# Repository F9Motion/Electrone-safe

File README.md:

# Electrone-safe
An Electronic safe with 4 numbers for password with Buzzer and Display for your snacs!

# Why I made this
My mechanical safe project was rejected so I just did electronic safe to protect my snacs.
# Features
* You can chose your password
* Display for comfort
* Protection with 4 numbers
* Custom safe
# How it works
PCB from this safe have 12 buttons(10 for numbers 3 for **ENTER** and **BACKSPACE**).
You can change your password in firmware(Soon I teach you how to do it). When you push your password firmware give command to motor and motor open safe and show text "CORRECT". And after a few moment motor close safe. When the password is incorrect safe don't open. Just give you chance to retry. And in display you see text "INCORRECT". Safe can't block but don't worry if someone try to write all combination he have to write 10 000 variants to unlock the safe. Your snacs is protected.
# How to assemble
1. Order part from BOM
2. Solder parts to PCB
3. Glue mount between case and door.
4. Flash Raspberry pi pico(read "HOW TO FLASH")
5. Place PCB to door mount.
6. Glue door mount to door
7. Put your snacs to safe!
# How to Flash
1. Download Arduino IDE
2. Open my firmware and find text **PASSWORD**
3. Change it
4. Connect pico to PC
5. Upload firmware just by clicking this button

# Bill Of Material(BOM)

|Name             |Price (without shipping)|Link (if item have a link)|
|-----------------|------------------------|--------------------------|
|Raspberry pi pico|$2.74                   |https://ali.click/bl02r1b |
|Printing PCB     |$4                      |JLCPCB                    |
|Buttons          |$2.46                   |https://ali.click/kr02r1y |
|Buzzer           |$1.64                   |https://ali.click/tt02r1c |
|Display          |$1.63                   |https://ali.click/ty02r1x |
|Battery          |$5.26                   |https://ali.click/z212r1b |
|Servo Motor      |$1.47                   |https://ali.click/q512r1s |
|buttons.step     |$0.08                   |felament price only       |
|case.step        |$8.65                   |felament price only       |
|door mount.step  |$0.05                   |felament price only       |
|door .step       |$2.22                   |felament price only       |
|mount.step       |$0.99                   |felament price only       |

# Credits
Programs: Blender, KiCad, Arduino IDE
Work: Rasul

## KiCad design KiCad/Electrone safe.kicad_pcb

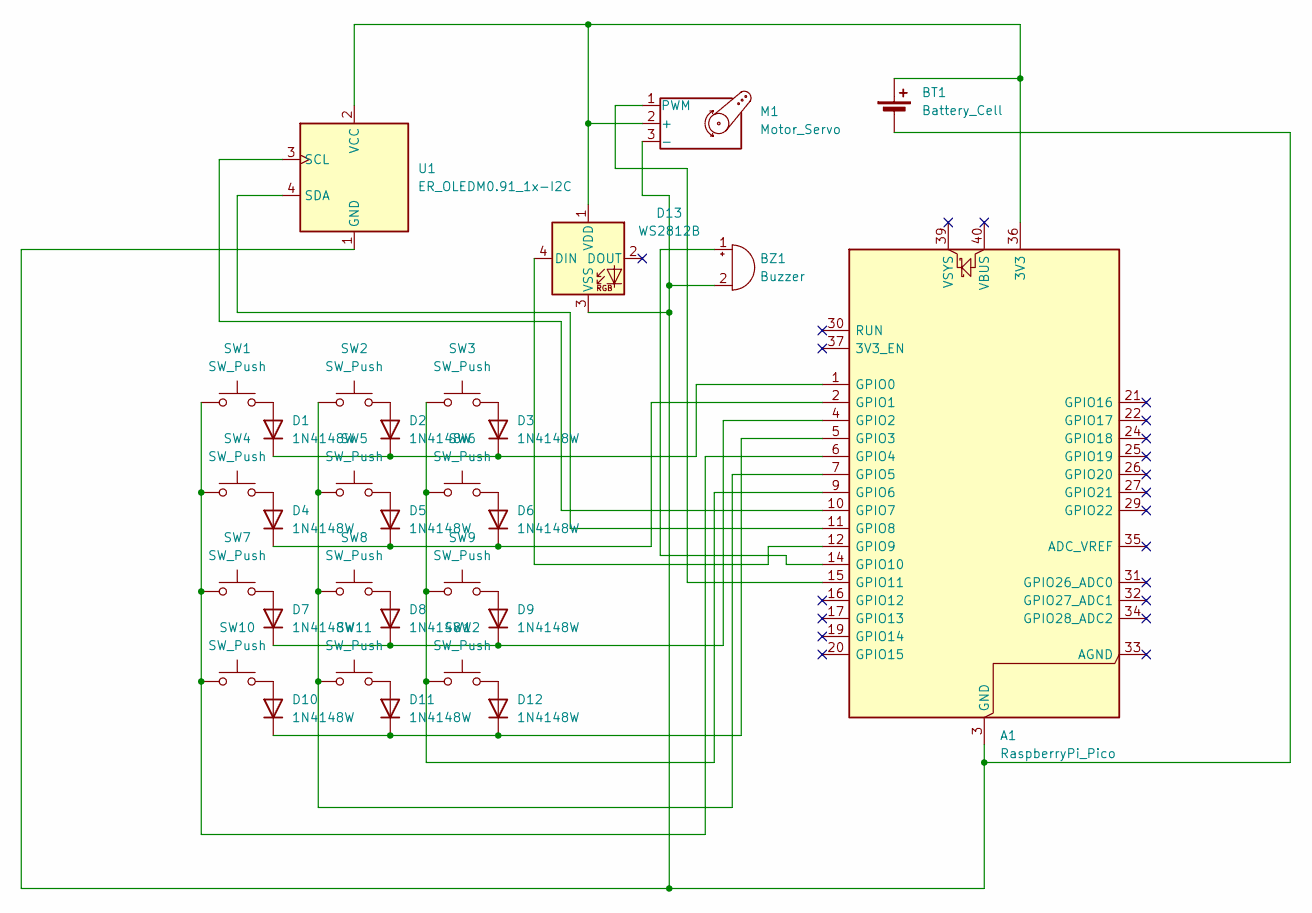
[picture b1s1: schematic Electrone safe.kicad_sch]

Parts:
A1: RaspberryPi_Pico; RaspberryPi_Pico_Common_Unspecified
BT1: Battery_Cell; Battery_Panasonic_CR1025-VSK_Vertical_CircularHoles
BZ1: Buzzer; Buzzer_12x9.5RM7.6
D1, D2, D3, D4, D5, D6, D7, D8, D9, D10, D11, D12: 1N4148W; D_SOD-123
D13: WS2812B; LED_WS2812B-2020_PLCC4_2.0x2.0mm
M1: Motor_Servo; Vybronics_VZ30C1T8219732L
SW1, SW2, SW3, SW4, SW5, SW6, SW7, SW8, SW9, SW10, SW11, SW12: SW_Push; SW_Push_1P1T_NO_E-Switch_TL3301NxxxxxG
U1: ER_OLEDM0.91_1x-I2C

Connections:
unnamed: A1.36 (3V3), BT1.1 (+), D13.1 (VDD), M1.2 (+), U1.2 (VCC)
unnamed: A1.1 (GPIO0), D1.1 (K), D2.1 (K), D3.1 (K)
unnamed: A1.2 (GPIO1), D4.1 (K), D5.1 (K), D6.1 (K)
unnamed: A1.4 (GPIO2), D7.1 (K), D8.1 (K), D9.1 (K)
unnamed: A1.5 (GPIO3), D10.1 (K), D11.1 (K), D12.1 (K)
unnamed: A1.6 (GPIO4), SW1.1, SW4.1, SW7.1, SW10.1
unnamed: A1.7 (GPIO5), SW2.1, SW5.1, SW8.1, SW11.1
unnamed: A1.9 (GPIO6), SW3.1, SW6.1, SW9.1, SW12.1
unnamed: A1.10 (GPIO7), U1.3 (SCL)
unnamed: A1.11 (GPIO8), U1.4 (SDA)
unnamed: A1.12 (GPIO9), D13.4 (DIN)
unnamed: A1.14 (GPIO10), BZ1.1 (+)
unnamed: A1.15 (GPIO11), M1.1 (PWM)
unnamed: A1.3 (GND), A1.8 (GND), A1.13 (GND), A1.18 (GND), A1.23 (GND), A1.28 (GND), A1.38 (GND), BT1.2 (-), BZ1.2 (-), D13.3 (VSS), M1.3 (-), U1.1 (GND)
unnamed: D1.2 (A), SW1.2
unnamed: D2.2 (A), SW2.2
unnamed: D3.2 (A), SW3.2
unnamed: D4.2 (A), SW4.2
unnamed: D5.2 (A), SW5.2
unnamed: D6.2 (A), SW6.2
unnamed: D7.2 (A), SW7.2
unnamed: D8.2 (A), SW8.2
unnamed: D9.2 (A), SW9.2
unnamed: D10.2 (A), SW10.2
unnamed: D11.2 (A), SW11.2
unnamed: D12.2 (A), SW12.2

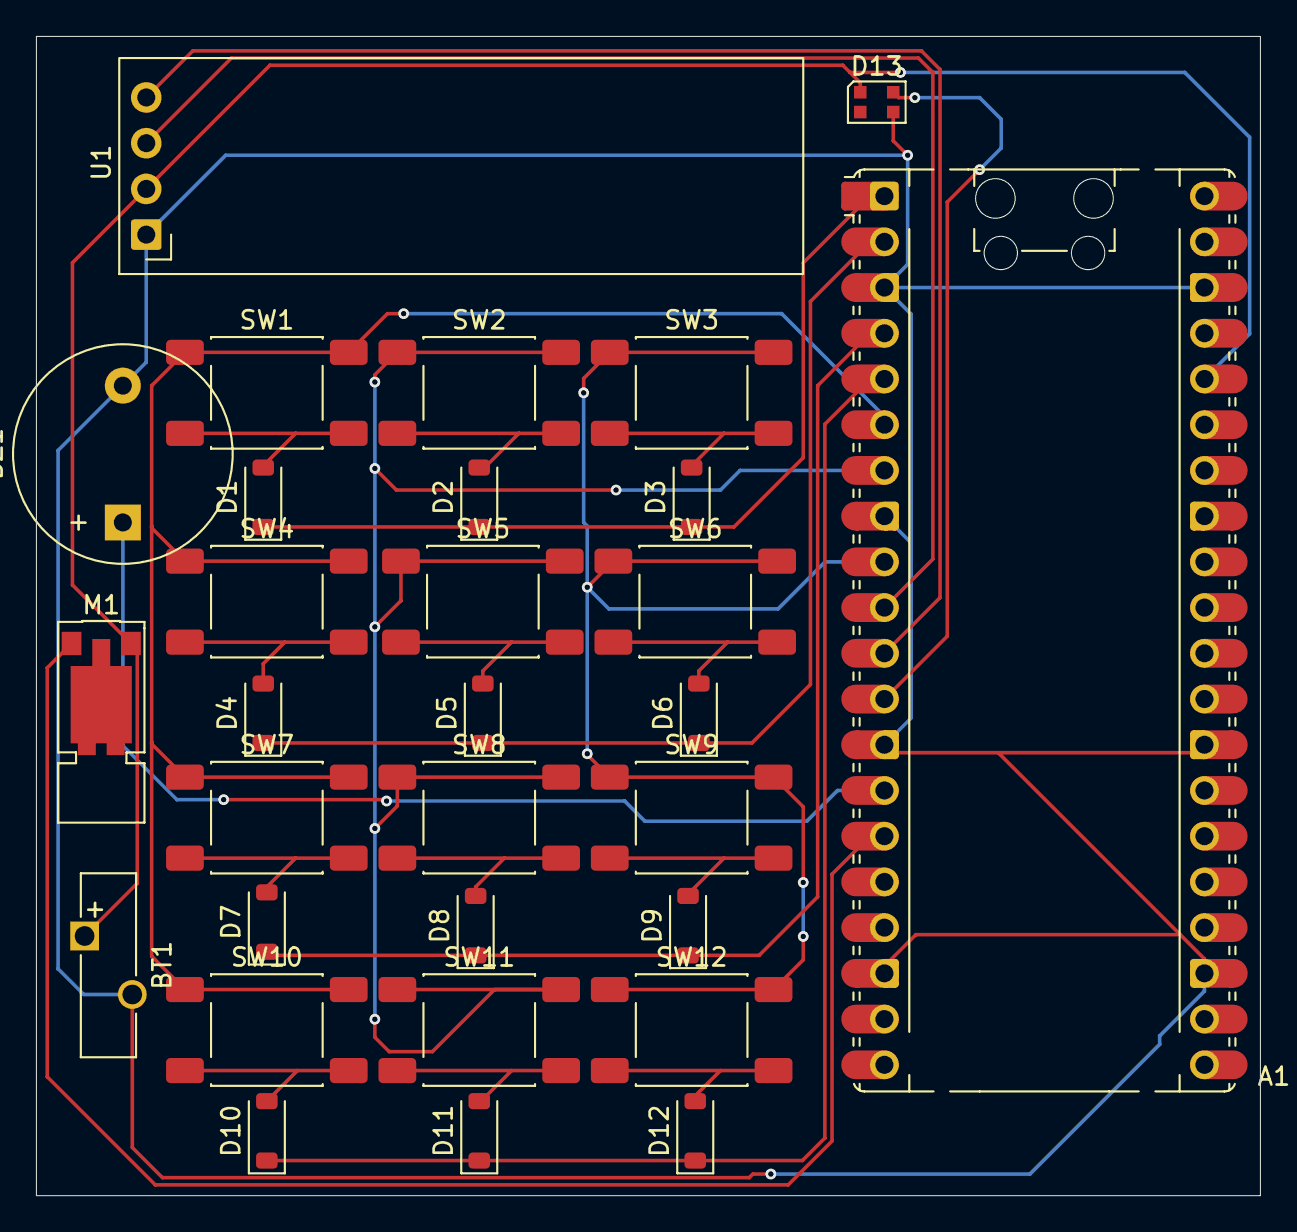
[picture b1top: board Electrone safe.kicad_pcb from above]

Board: 2 copper layers, 68.0 x 64.4 mm, 30 parts (0 on the bottom side), 26 nets.
